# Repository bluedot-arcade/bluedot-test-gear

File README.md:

<p align="right">

</p>
<br><br>
<p align="center">
    <h1 align="center">BlueDot Test Gear</h1>
    <p align="center">This repository contains the source code and the design files for the bluedot automated test gear.</p>
    <p align="center"><strong><a href="https://docs.bluedotarcade.com/boards/bd845-pwb">Explore the docs</a></strong></p>
    <br><br>
</p>

## Testers

- [BD845-PWB Tester](/bd845-pwb-tester/)

## License

Distributed under the MIT License. See [LICENSE.txt] for more information.

<p align="right">(<a href="#readme-top">back to top</a>)</p>

[LICENSE.txt]: /LICENSE.txt
[PlatformIO Core Docs]: https://docs.platformio.org/en/latest/core/index.html
[PlatformIO Docs]: https://docs.platformio.org/

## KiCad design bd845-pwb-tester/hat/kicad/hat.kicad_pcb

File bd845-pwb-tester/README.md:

<p align="right">

</p>
<br><br>
<p align="center">
    <h1 align="center">BD845-PWB Tester</h1>
    <p align="center">This repository contains the source code and the design files of the BD845-PWB Tester.</p>
    <p align="center"><strong><a href="https://github.com/bluedot-arcade/bd845-pwb-board">Go to board repository</a></strong></p>
    <p align="center"><strong><a href="https://docs.bluedotarcade.com/boards/bd845-pwb">Explore the docs</a></strong></p>
    <br><br>
</p>

## About the project

The BD845-PWB Tester is a test gear specifically designed to automate the [BD845-PWB] board physical tests. 

It is based on an Arduino Mega (or any compatible board). An additional hat is provided to avoid a flying wires setup and speed up the testing procedure.

<p align="right">(<a href="#readme-top">back to top</a>)</p>

## Test procedure

This section describes the steps required to perform the tests.

### 1. Build and upload test program to the Arduino Mega

This project uses PlatformIO to build and upload the project. Only the PlatformIO Core CLI is required but consider installing the PlatformIO IDE for a better user experience.

The following is the recommended way to build and upload the firmware.

1. [Install PlatformIO Core.][PlatformIO Core Docs]

2. Clone the repository.
    ```bash
    git clone https://github.com/bluedot-arcade/bluedot-test-gear
    ```

3. Navigate to the root of the project.
   ```bash
    cd bluedot-test-gear/bd845-pwb-tester
    ```

4. Build the project. Binaries will be created inside the `.pio` folder.
    ```bash
    platformio run
    ```
    
5. Upload the project to the Arduino Mega.
    ```bash
    platformio run --target upload
    ```

If you prefer using the Arduino IDE the full code is contained in `src/main.cpp`. Just rename it to `main.ino`.

<p align="right">(<a href="#readme-top">back to top</a>)</p>

### 2. Set up test gear

Wire the Arduino Mega to the BD845-PWB. This does not require any additional components other than wires for direct connection of the pins.

Alternatively you can use the provided hat.

The following is the Arduino Mega <-> BD845-PWB pins mapping table.

| Arduino Mega Pin | BD845-PWB Pin | | Arduino Mega Pin | BD845-PWB Pin |
| ---------------- | ------------- |-| ---------------- | ------------- |
| A0               | U_OUT         |-| D37              | L_S1          |
| A1               | D_OUT         |-| D36              | L_S2          |
| A2               | L_OUT         |-| D35              | L_S3          |
| A3               | R_OUT         |-| D34              | L_S4          |
| A4               | C_OUT         |-| D33              | R_S1          |
| A8               | FL1           |-| D32              | R_S2          |
| A9               | FL2           |-| D31              | R_S3          |
| A10              | FL3           |-| D30              | R_S4          |
| A11              | FL4           |-| D53              | C_S1          |
| A12              | FL5           |-| D52              | C_S2          |
| A13              | TEST          |-| D51              | C_S3          |
| D22              | U_S1          |-| D50              | C_S4          |
| D23              | U_S2          |-| D49              | U_LIGHT       |
| D24              | U_S3          |-| D48              | D_LIGHT       |
| D25              | U_S4          |-| D47              | L_LIGHT       |
| D26              | D_S1          |-| D46              | R_LIGHT       |
| D27              | D_S2          |-| D45              | C_LIGHT       |
| D28              | D_S3          |-|
| D29              | D_S4          |-|

The full pinout for the BD845-PWB can be found in the [docs][BD845-PWB Docs].

<p align="right">(<a href="#readme-top">back to top</a>)</p>

### 3. Run test routines

Test routines can be run using a serial monitor from a computer.

1. Connect the Arduino Mega to a computer with a USB cable.
2. Connect the BD845-PWB power connector to a +12V supply.
3. On the computer open the serial monitor, open the Arduino Mega serial port and set the baud rate to 115200. A menu with all test routines will be printed.
   
    ```bash
    *** BD845-PWB Test Routines ***

    Select option:
    1. Test inputs
    2. Test lights external
    3. Test lights press mode
    4. Test debounce
    5. Test legacy
    ```
4. Select the routine to run by writing the corresponding number to the serial monitor.
5. "TEST SUCCESSFUL" will be printed on success. Otherwise "TEST FAILED" will be printed and the built-in LED on Arduino Mega will light up.

<p align="right">(<a href="#readme-top">back to top</a>)</p>

## Hat board

The [/hat](hat/) folder contains the project files for an hat board that simplifies the connection between the Arduino Mega and the BD845-PWB board, speeding up testing without the use of stray wires.

It also comes with additional LED indicators for test status and light driver tests.

## License

Distributed under the MIT License. See [LICENSE.txt] for more information.

<p align="right">(<a href="#readme-top">back to top</a>)</p>

[LICENSE.txt]: /LICENSE.txt
[PlatformIO Core Docs]: https://dohttps://docs.bluedotarcade.com/boards/bd845-pwbcs.platformio.org/en/latest/core/index.html
[PlatformIO Docs]: https://docs.platformio.org/
[BD845-PWB]: https://github.com/bluedot-arcade/bd845-pwb-board
[BD845-PWB Docs]: https://docs.bluedotarcade.com/boards/bd845-pwb

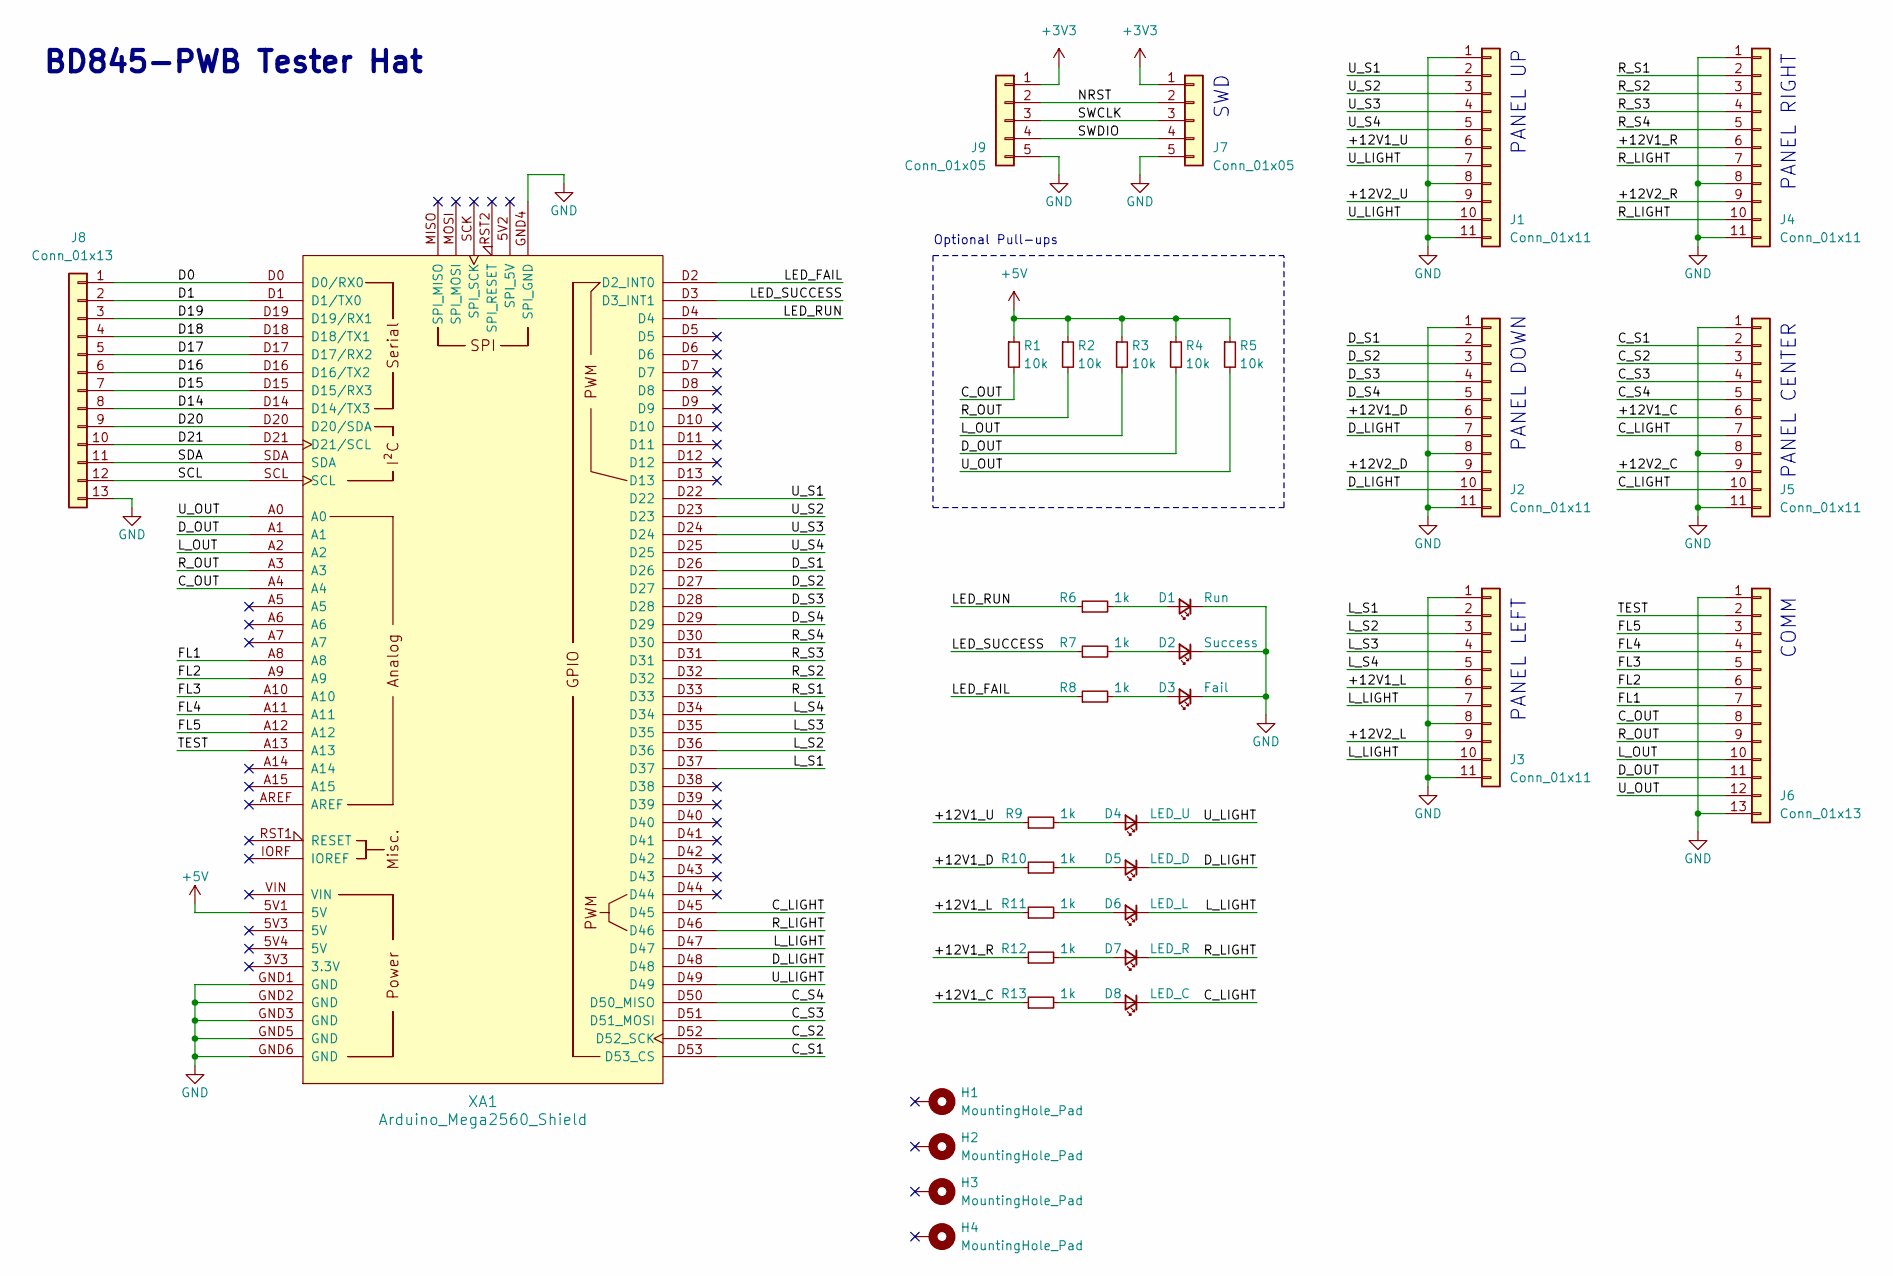
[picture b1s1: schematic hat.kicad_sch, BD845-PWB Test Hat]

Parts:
D1: Run; LED_D3.0mm
D2: Success; LED_D3.0mm
D3: Fail; LED_D3.0mm
D4: LED_U; LED_D3.0mm
D5: LED_D; LED_D3.0mm
D6: LED_L; LED_D3.0mm
D7: LED_R; LED_D3.0mm
D8: LED_C; LED_D3.0mm
H1, H2, H3, H4: MountingHole_Pad; MountingHole_4mm
J1, J2, J3, J4, J5: Conn_01x11; PinHeader_1x11_P2.54mm_Vertical
J6, J8: Conn_01x13; PinHeader_1x13_P2.54mm_Vertical
J7, J9: Conn_01x05; PinHeader_1x05_P2.54mm_Vertical
R1, R2, R3, R4, R5: 10k; R_Axial_DIN0207_L6.3mm_D2.5mm_P10.16mm_Horizontal
R6, R7, R8, R9, R10, R11, R12, R13: 1k; R_Axial_DIN0207_L6.3mm_D2.5mm_P10.16mm_Horizontal
XA1: Arduino_Mega2560_Shield

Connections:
+3V3: J7.1, J9.1
+5V: R1.1, R2.1, R3.1, R4.1, R5.1, XA1.5V1 (5V)
/+12V1_C: J5.6, R13.1
/+12V1_D: J2.6, R10.1
/+12V1_L: J3.6, R11.1
/+12V1_R: J4.6, R12.1
/+12V1_U: J1.6, R9.1
/+12V2_C: J5.9
/+12V2_D: J2.9
/+12V2_L: J3.9
/+12V2_R: J4.9
/+12V2_U: J1.9
/C_LIGHT: D8.1 (K), J5.7, J5.10, XA1.D45
/C_OUT: J6.8, R1.2, XA1.A4
/C_S1: J5.2, XA1.D53 (D53_CS)
/C_S2: J5.3, XA1.D52 (D52_SCK)
/C_S3: J5.4, XA1.D51 (D51_MOSI)
/C_S4: J5.5, XA1.D50 (D50_MISO)
/D0: J8.1, XA1.D0 (D0/RX0)
/D1: J8.2, XA1.D1 (D1/TX0)
/D14: J8.8, XA1.D14 (D14/TX3)
/D15: J8.7, XA1.D15 (D15/RX3)
/D16: J8.6, XA1.D16 (D16/TX2)
/D17: J8.5, XA1.D17 (D17/RX2)
/D18: J8.4, XA1.D18 (D18/TX1)
/D19: J8.3, XA1.D19 (D19/RX1)
/D20: J8.9, XA1.D20 (D20/SDA)
/D21: J8.10, XA1.D21 (D21/SCL)
/D_LIGHT: D5.1 (K), J2.7, J2.10, XA1.D48
/D_OUT: J6.11, R4.2, XA1.A1
/D_S1: J2.2, XA1.D26
/D_S2: J2.3, XA1.D27
/D_S3: J2.4, XA1.D28
/D_S4: J2.5, XA1.D29
/FL1: J6.7, XA1.A8
/FL2: J6.6, XA1.A9
/FL3: J6.5, XA1.A10
/FL4: J6.4, XA1.A11
/FL5: J6.3, XA1.A12
/LED_FAIL: R8.1, XA1.D2 (D2_INT0)
/LED_RUN: R6.1, XA1.D4
/LED_SUCCESS: R7.1, XA1.D3 (D3_INT1)
/L_LIGHT: D6.1 (K), J3.7, J3.10, XA1.D47
/L_OUT: J6.10, R3.2, XA1.A2
/L_S1: J3.2, XA1.D37
/L_S2: J3.3, XA1.D36
/L_S3: J3.4, XA1.D35
/L_S4: J3.5, XA1.D34
/NRST: J7.2, J9.2
/R_LIGHT: D7.1 (K), J4.7, J4.10, XA1.D46
/R_OUT: J6.9, R2.2, XA1.A3
/R_S1: J4.2, XA1.D33
/R_S2: J4.3, XA1.D32
/R_S3: J4.4, XA1.D31
/R_S4: J4.5, XA1.D30
/SCL: J8.12, XA1.SCL
/SDA: J8.11, XA1.SDA
/SWCLK: J7.3, J9.3
/SWDIO: J7.4, J9.4
/TEST: J6.2, XA1.A13
/U_LIGHT: D4.1 (K), J1.7, J1.10, XA1.D49
/U_OUT: J6.12, R5.2, XA1.A0
/U_S1: J1.2, XA1.D22
/U_S2: J1.3, XA1.D23
/U_S3: J1.4, XA1.D24
/U_S4: J1.5, XA1.D25
GND: D1.1 (K), D2.1 (K), D3.1 (K), J1.1, J1.8, J1.11, J2.1, J2.8, J2.11, J3.1, J3.8, J3.11, J4.1, J4.8, J4.11, J5.1, J5.8, J5.11, J6.1, J6.13, J7.5, J8.13, J9.5, XA1.GND1 (GND), XA1.GND2 (GND), XA1.GND3 (GND), XA1.GND4 (SPI_GND), XA1.GND5 (GND), XA1.GND6 (GND)
unnamed: D1.2 (A), R6.2
unnamed: D2.2 (A), R7.2
unnamed: D3.2 (A), R8.2
unnamed: D4.2 (A), R9.2
unnamed: D5.2 (A), R10.2
unnamed: D6.2 (A), R11.2
unnamed: D7.2 (A), R12.2
unnamed: D8.2 (A), R13.2

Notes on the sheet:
BD845-PWB Tester Hat
Optional Pull-ups
COMM
SWD
PANEL LEFT
PANEL CENTER
PANEL UP
PANEL RIGHT
PANEL DOWN

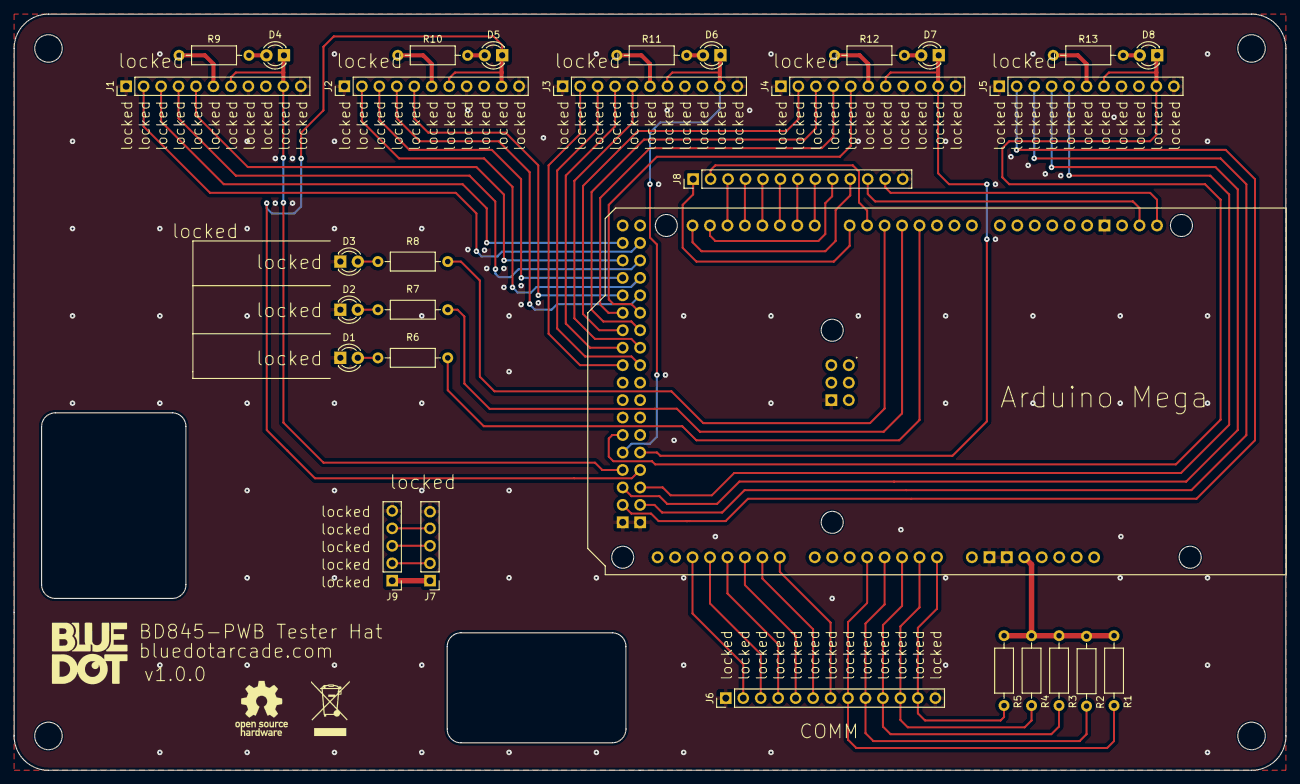
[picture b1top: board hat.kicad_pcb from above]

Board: 2 copper layers, 185.0 x 110.0 mm, 35 parts (1 on the bottom side), 70 nets.

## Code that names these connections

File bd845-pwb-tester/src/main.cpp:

#include <Arduino.h>

/* Compile options */
// #define USE_EXTERNAL_PULLUPS

/* Commands */

#define CMD_TEST_INPUTS '1'
#define CMD_TEST_LIGHTS_EXT '2'
#define CMD_TEST_LIGHTS_PRESS '3'
#define CMD_TEST_DEBOUNCE '4'
#define CMD_TEST_LEGACY '5'

/* States */
#define STATE_IDLE 0
#define STATE_TEST_RUNNING 1
#define STATE_TEST_FAILED 2
#define STATE_TEST_SUCCESSFUL 3

/* 
 * Map Arduino Mega pins to BD845-PWB pins.
 * The pinout for the BD845-PWB can be found here 
 * https://docs.bluedotarcade.com/boards/bd845-pwb
 */

/* Comm inputs */

#define FL1       PK0
#define FL2       PK1
#define FL3       PK2
#define FL4       PK3
#define FL5       PK4
#define TEST      PK5
#define IN_DDR    DDRK
#define IN_PORT   PORTK
#define IN_OFFSET 0

/* Comm outputs */

#define U_OUT      PF0 
#define D_OUT      PF1 
#define L_OUT      PF2 
#define R_OUT      PF3 
#define C_OUT      PF4 
#define OUT_DDR    DDRF
#define OUT_PIN    PINF
#define OUT_OFFSET 0

/* Panel up sensors */

#define U_S1     PA0 
#define U_S2     PA1 
#define U_S3     PA2 
#define U_S4     PA3 
#define U_DDR    DDRA
#define U_PORT   PORTA
#define U_OFFSET 0

/* Panel down sensors */

#define D_S1     PA4 
#define D_S2     PA5 
#define D_S3     PA6 
#define D_S4     PA7 
#define D_DDR    DDRA
#define D_PORT   PORTA
#define D_OFFSET 4

/* Panel left sensors */

#define L_S1     PC0 
#define L_S2     PC1 
#define L_S3     PC2 
#define L_S4     PC3 
#define L_DDR    DDRC
#define L_PORT   PORTC
#define L_OFFSET 0

/* Panel right sensors */

#define R_S1     PC4 
#define R_S2     PC5 
#define R_S3     PC6 
#define R_S4     PC7 
#define R_DDR    DDRC
#define R_PORT   PORTC3
#define R_OFFSET 4

/* Panel center sensors */

#define C_S1     PB0 
#define C_S2     PB1 
#define C_S3     PB2 
#define C_S4     PB3 
#define C_DDR    DDRB
#define C_PORT   PORTB
#define C_OFFSET 0

/* Lights */

#define U_LIGHT      PL0 
#define D_LIGHT      PL1 
#define L_LIGHT      PL2 
#define R_LIGHT      PL3 
#define C_LIGHT      PL4
#define LIGHT_DDR    DDRL
#define LIGHT_PIN    PINL
#define LIGHT_OFFSET 0

/* Hat pins */

#define LED_FAIL    PE4
#define LED_SUCCESS PE5
#define LED_RUN     PE6 

void setupSerialPort();
void setupLeds();
void setupCommInputPins();
void setupCommOutputPins();
void setupUpPins();
void setupDownPins();
void setupLeftPins();
void setupRightPins();
void setupCenterPins();
void setupLightPins();

bool testInputs();
bool testLightsExt();
bool testLightsPress();
bool testDebounce();
bool testLegacy();

uint8_t readCommOutputPins();
uint8_t readLightPins();
void setCommInputPins(uint8_t state);
void setUpPins(uint8_t state);
void setDownPins(uint8_t state);
void setLeftPins(uint8_t state);
void setRightPins(uint8_t state);
void setCenterPins(uint8_t state);
void setHighZ(int pin);
void printMenu();
void setState(uint8_t state);

// Setup ---------------------------------------------------------------

void setup() {
  setupSerialPort();
  setupLeds();

  setupCommInputPins();
  setupCommOutputPins();
  
  setupUpPins();
  setupDownPins();
  setupLeftPins();
  setupRightPins();
  setupLightPins();
}

void setupSerialPort() {
  Serial.begin(115200);
}

void setupLeds() {
  pinMode(LED_BUILTIN, OUTPUT);
  digitalWrite(LED_BUILTIN, LOW);
  
  pinMode(LED_FAIL, OUTPUT);
  digitalWrite(LED_FAIL, LOW);

  pinMode(LED_SUCCESS, OUTPUT);
  digitalWrite(LED_SUCCESS, LOW);

  pinMode(LED_RUN, OUTPUT);
  digitalWrite(LED_RUN, LOW);
}

void setupCommInputPins() {
  setHighZ(TEST);
  setHighZ(FL5);
  setHighZ(FL4);
  setHighZ(FL3);
  setHighZ(FL2);
  setHighZ(FL1);
}

void setupCommOutputPins() {
  #ifdef USE_EXTERNAL_PULLUPS
  pinMode(C_OUT, INPUT);
  pinMode(R_OUT, INPUT);
  pinMode(L_OUT, INPUT);
  pinMode(D_OUT, INPUT);
  pinMode(U_OUT, INPUT);
  #else
  pinMode(C_OUT, INPUT_PULLUP);
  pinMode(R_OUT, INPUT_PULLUP);
  pinMode(L_OUT, INPUT_PULLUP);
  pinMode(D_OUT, INPUT_PULLUP);
  pinMode(U_OUT, INPUT_PULLUP);
  #endif
}

void setupUpPins() {
  setHighZ(U_S1);pinMode(LED_FAIL, OUTPUT);
  digitalWrite(LED_FAIL, LOW);
  setHighZ(U_S2);
  setHighZ(U_S3);
  setHighZ(U_S4);
}

void setupDownPins() {
  setHighZ(U_S1);
  setHighZ(U_S2);
  setHighZ(U_S3);
  setHighZ(U_S4);
}

void setupLeftPins() {
  setHighZ(U_S1);
  setHighZ(U_S2);
  setHighZ(U_S3);
  setHighZ(U_S4);
}

void setupRightPins() {
  setHighZ(U_S1);
  setHighZ(U_S2);
  setHighZ(U_S3);
  setHighZ(U_S4);
}

void setupCenterPins() {
  setHighZ(U_S1);
  setHighZ(U_S2);
  setHighZ(U_S3);
  setHighZ(U_S4);
}

void setupLightPins() {
  pinMode(U_LIGHT, INPUT_PULLUP);
  pinMode(D_LIGHT, INPUT_PULLUP);
  pinMode(L_LIGHT, INPUT_PULLUP);
  pinMode(R_LIGHT, INPUT_PULLUP);
  pinMode(C_LIGHT, INPUT_PULLUP);
}

// Loop ----------------------------------------------------------------

void loop() {
  //Serial.flush();
  printMenu();

  // Wait for command
  while(Serial.available() <= 0);

  setState(STATE_IDLE);
  char cmd = Serial.read();
  bool successful = true;
 
  switch(cmd) {
    case CMD_TEST_INPUTS:
      setState(STATE_TEST_RUNNING);
      successful = testInputs();
      break;
    case CMD_TEST_LIGHTS_EXT:
      setState(STATE_TEST_RUNNING);
      successful = testLightsExt();
      break;
    case CMD_TEST_LIGHTS_PRESS:
      setState(STATE_TEST_RUNNING);
      successful = testLightsPress();
      break;
    case CMD_TEST_DEBOUNCE:
      setState(STATE_TEST_RUNNING);
      successful = testDebounce();
      break;
    case CMD_TEST_LEGACY:
      setState(STATE_TEST_RUNNING);
      successful = testLegacy();
      break;
    default:
      Serial.println(F("Command not found!"));
      return;
  }

  if(successful) {
    setState(STATE_TEST_SUCCESSFUL);
    Serial.println(F("TEST SUCCESSFUL"));
  } else {
    setState(STATE_TEST_FAILED);
    Serial.println(F("TEST FAILED"));
  }
}

bool testInputs() {
  uint8_t up = 0;
  uint8_t down = 0;
  uint8_t left = 0;
  uint8_t right = 0;
  uint8_t center = 0;

  setUpPins(up);
  setDownPins(down);
  setLeftPins(left);
  setRightPins(right);
  setCenterPins(center);

  if(readCommOutputPins() != 0)
    return false;
  
  while(++up < 0x10) {
    setUpPins(up);

    if(readCommOutputPins() != U_OUT)
      return false;
  }

  return true;
}

bool testLightsExt() {
  Serial.println(F("Testing lights external..."));
  uint8_t inputs = 0;
  uint8_t lights = 0;
  uint8_t expected = 0;

  while(inputs < 0x20) {
    setCommInputPins(inputs);
    delay(1);
    lights = readLightPins();
    expected = ~inputs & 0x1F;
    
    if(lights != expected) {
      Serial.print(F("inputs: "));
      Serial.print(inputs, HEX);
      Serial.print(F(", lights: "));
      Serial.print(lights, HEX);
      Serial.print(F(", expected: "));
      Serial.print(expected, HEX);
      Serial.println();
      return false;
    }
    
    inputs++;
  }

  return true;
}

bool testLightsPress() {
  return true;
}

bool testDebounce() {
  return true;
}

bool testLegacy() {

  return true;
}

// Utilities -----------------------------------------------------------

uint8_t readCommOutputPins() {
  return OUT_PIN & (0x1F << OUT_OFFSET);
}

uint8_t readLightPins() {
  return LIGHT_PIN & (0x1F << LIGHT_OFFSET);
}

void setCommInputPins(uint8_t state) {
  IN_DDR = (IN_DDR & (0xC0 >> IN_OFFSET)) | (state << IN_OFFSET);
}

void setUpPins(uint8_t state) {
  U_DDR = (U_DDR & (0xF0 >> U_OFFSET)) | (state << U_OFFSET);
}

void setDownPins(uint8_t state) {
  D_DDR = (D_DDR & (0xF0 >> D_OFFSET)) | (state << D_OFFSET);
}

void setLeftPins(uint8_t state) {
  L_DDR = (L_DDR & (0xF0 >> L_OFFSET)) | (state << L_OFFSET);
}

void setRightPins(uint8_t state) {
  R_DDR = (R_DDR & (0xF0 >> R_OFFSET)) | (state << R_OFFSET);
}

void setCenterPins(uint8_t state) {
  C_DDR = (C_DDR & (0xF0 >> C_OFFSET)) | (state << C_OFFSET);
}

void setHighZ(int pin) {
  digitalWrite(pin, LOW);
  pinMode(pin, INPUT);
}

void printMenu() {
  Serial.println(F("\n*** BD845-PWB Test Routines ***\n"));
  Serial.println(F("Select option:"));
  Serial.println(F("1. Test inputs"));
  Serial.println(F("2. Test lights external"));
  Serial.println(F("3. Test lights press mode"));
  Serial.println(F("4. Test debounce"));
  Serial.println(F("5. Test legacy"));
  Serial.println();
}

void setState(uint8_t state) {
  switch(state) {
    case STATE_IDLE:
      digitalWrite(LED_BUILTIN, LOW);
      digitalWrite(LED_FAIL, LOW);
      digitalWrite(LED_SUCCESS, LOW);
      digitalWrite(LED_RUN, LOW);
      break;
    case STATE_TEST_RUNNING:
      digitalWrite(LED_BUILTIN, LOW);
      digitalWrite(LED_FAIL, LOW);
      digitalWrite(LED_SUCCESS, LOW);
      digitalWrite(LED_RUN, HIGH);
      break;
    case STATE_TEST_FAILED:
      digitalWrite(LED_BUILTIN, HIGH);
      digitalWrite(LED_FAIL, HIGH);
      digitalWrite(LED_SUCCESS, LOW);
      digitalWrite(LED_RUN, LOW);
      break;
    case STATE_TEST_SUCCESSFUL:
      digitalWrite(LED_BUILTIN, LOW);
      digitalWrite(LED_FAIL, LOW);
      digitalWrite(LED_SUCCESS, HIGH);
      digitalWrite(LED_RUN, LOW);
      break;
  }
}

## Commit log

2023-06-05 Import project.
2023-06-05 Update README.md.
2023-06-05 Import hat project.
2023-06-06 Fix pinout and add hat picture.
2023-06-06 Hat board v1.0.0.
2023-06-06 Update rules.
2023-06-06 Fix wrong pin defines.
2023-06-06 Update pin defines. Add state management function. Add external pullup compilation option.

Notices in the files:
README.md:
License: MIT
